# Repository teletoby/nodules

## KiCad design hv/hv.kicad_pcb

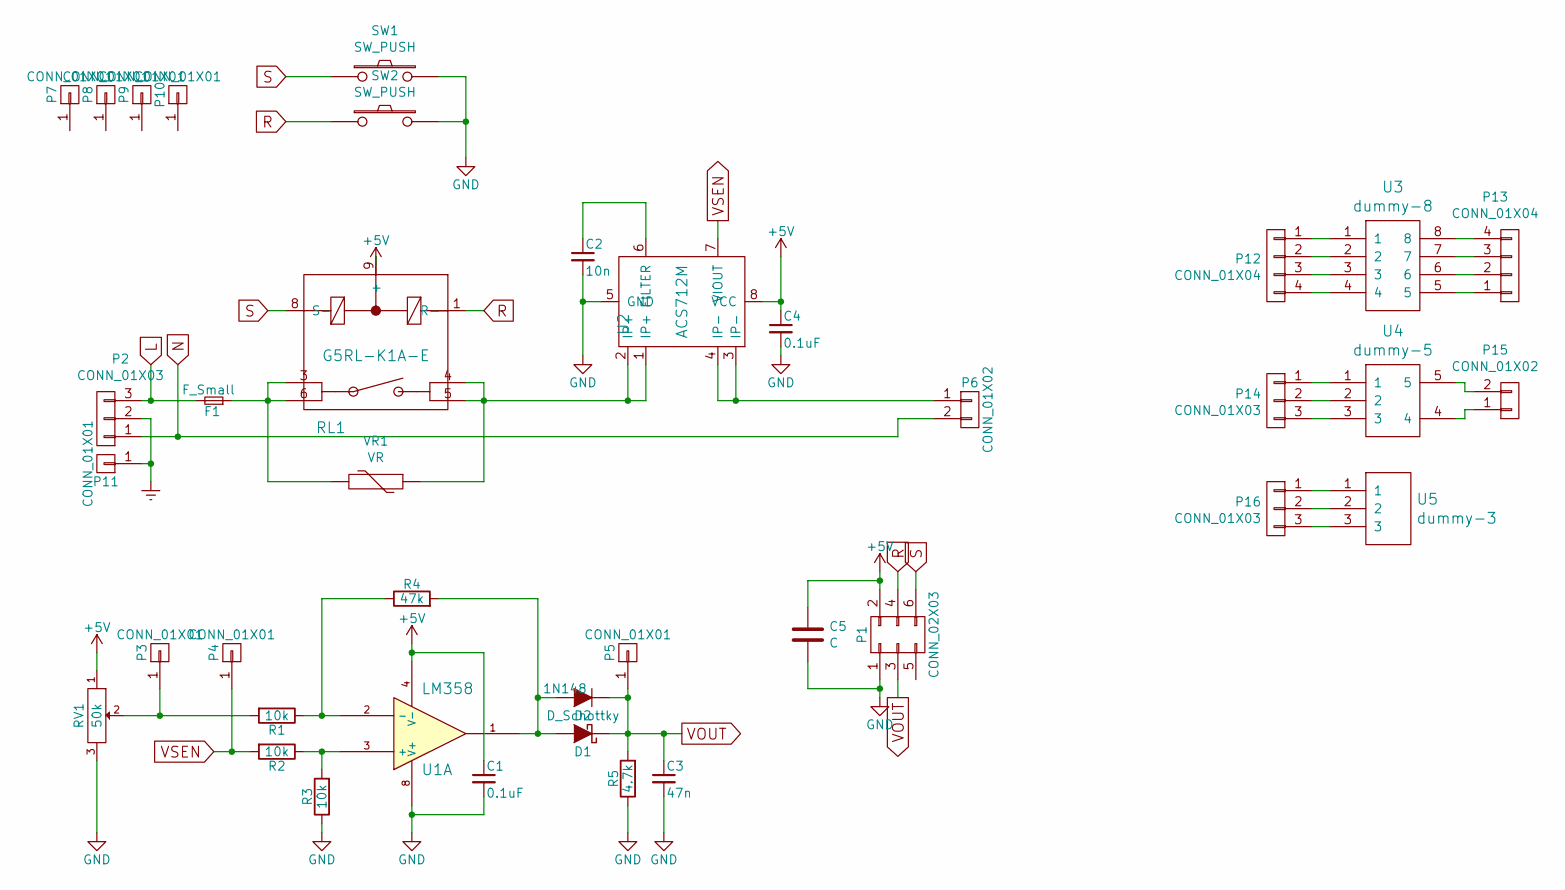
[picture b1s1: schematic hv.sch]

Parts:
C1, C4: 0.1uF; C_0805
C2: 10n; C_0805
C3: 47n; C_0805
C5: C; C_0805
D1: D_Schottky; SOD-323
D2: 1N148; Diode_DO-41_SOD81_Vertical_AnodeUp
F1: F_Small; Fuseholder5x20_horiz_open_inline_Type-I
P1: CONN_02X03; Pin_Header_Straight_2x03
P2: CONN_01X03; bornier3
P3, P4, P5, P11: CONN_01X01; Pin_Header_Straight_1x01
P6: CONN_01X02; bornier2
P7, P8, P9, P10: CONN_01X01; 1pin
P12, P13: CONN_01X04; Pin_Header_Straight_1x04
P14, P16: CONN_01X03; Pin_Header_Straight_1x03
P15: CONN_01X02; Pin_Header_Straight_1x02
R1, R2, R3: 10k; R_0805
R4: 47k; R_0805
R5: 4.7k; R_0805
RL1: G5RL-K1A-E
RV1: 50k; ART-3361P
SW1, SW2: SW_PUSH; SW_PUSH_SMALL
U1: LM358; SOIC-8_3.9x4.9mm_Pitch1.27mm
U2: ACS712M; SOIC-8_3.9x4.9mm_Pitch1.27mm
U3: dummy-8; SOIC_08_4.0mm_5.0mm_1.27mm
U4: dummy-5; SOT-23-5
U5: dummy-3; SOT-23-3
VR1: VR; RV_Disc_D12_W3.9_P7.5

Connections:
+5V: C1.1, C4.1, C5.1, P1.2, RL1.9 (+), RV1.1, U1.4 (V-), U2.8 (VCC)
Earth: P2.2, P11.1
GND: C1.2, C2.2, C3.2, C4.2, C5.2, P1.1, R3.1, R5.1, RV1.3, SW1.2, SW2.2, U1.8 (V+), U2.5 (GND)
L: F1.2, P2.3
N: P2.1, P6.2
unnamed: C2.1, U2.6 (FILTER)
unnamed: D1.2 (A), D2.2 (A), R4.2, U1.1
unnamed: F1.1, RL1.3, RL1.6, VR1.2
unnamed: P3.1, R1.2, RV1.2
unnamed: P6.1, U2.3 (IP-), U2.4 (IP-)
unnamed: P12.1, U3.1
unnamed: P12.2, U3.2
unnamed: P12.3, U3.3
unnamed: P12.4, U3.4
unnamed: P13.1, U3.5
unnamed: P13.2, U3.6
unnamed: P13.3, U3.7
unnamed: P13.4, U3.8
unnamed: P14.1, U4.1
unnamed: P14.2, U4.2
unnamed: P14.3, U4.3
unnamed: P15.1, U4.4
unnamed: P15.2, U4.5
unnamed: P16.1, U5.1
unnamed: P16.2, U5.2
unnamed: P16.3, U5.3
unnamed: R1.1, R4.1, U1.2 (-)
unnamed: R2.1, R3.2, U1.3 (+)
unnamed: RL1.4, RL1.5, U2.1 (IP+), U2.2 (IP+), VR1.1
R: P1.4, RL1.1 (R-), SW2.1
S: P1.6, RL1.8 (S-), SW1.1
VOUT: C3.1, D1.1 (K), D2.1 (K), P1.3, P5.1, R5.2
VSEN: P4.1, R2.2, U2.7 (VIOUT)

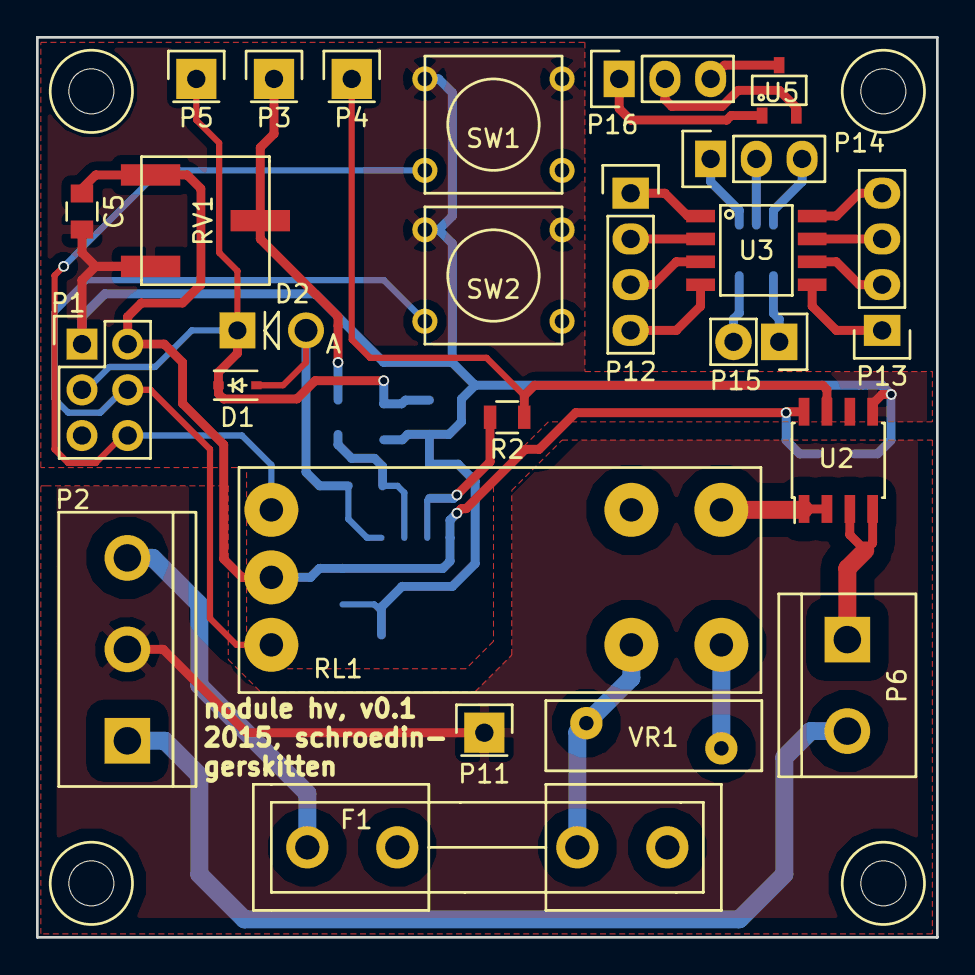
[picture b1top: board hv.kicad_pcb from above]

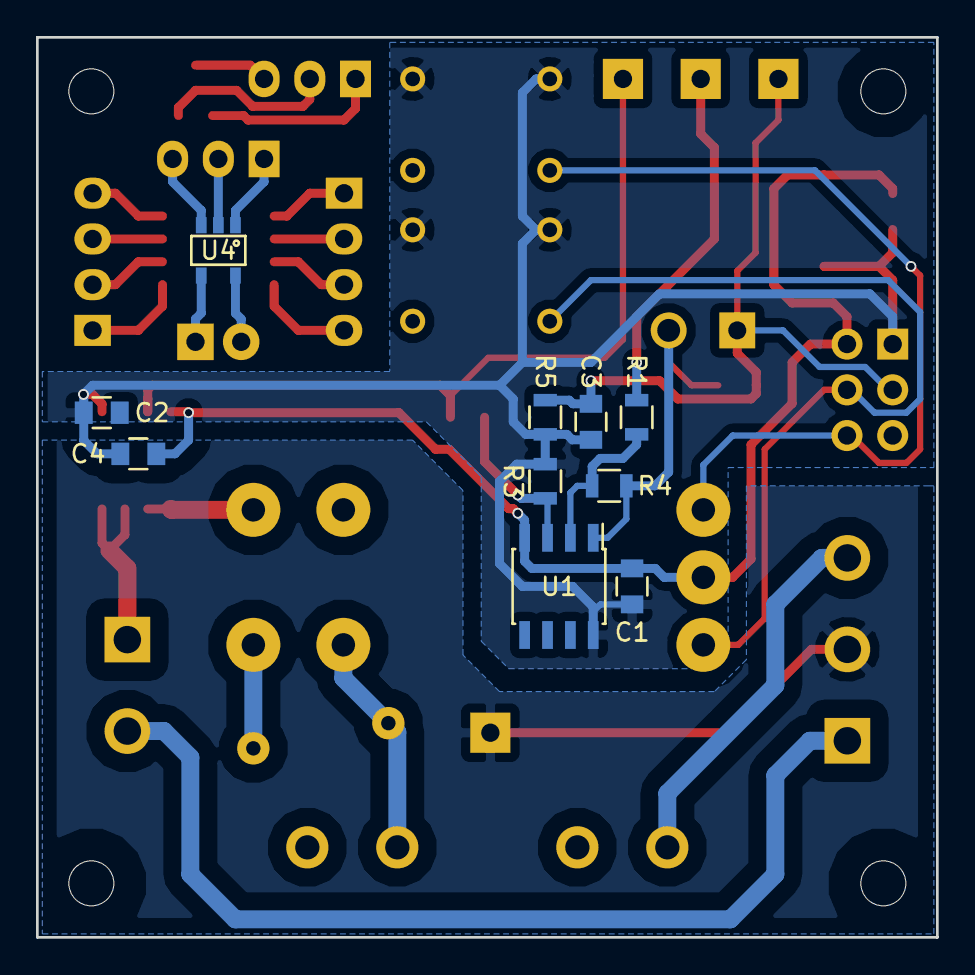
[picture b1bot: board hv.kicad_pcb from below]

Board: 2 copper layers, 50.0 x 50.0 mm, 39 parts (10 on the bottom side), 33 nets.

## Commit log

2015-12-12 Initial commit.
2015-12-12 Add license
2015-12-13 Add low-voltage module
2015-12-20 Rerouting on 5x5 cm2
2015-12-20 Change paths
2016-01-03 Generate gerbers and rename accoring to seeed specifications.
